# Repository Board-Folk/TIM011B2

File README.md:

# TIM-011B Version 2

A new updated remake of the TIM-011 computer from Serbia.

This repository contains the Bill-of-Materials (BOM), Gerbers and Kicad files for the new colour-capable, updated remake of the TIM-011 from the Mihajlo Pupin Institute of Serbia, 1987.

The original TIM-011 is a CP/M based computer that uses the Z80 family Hitachi HD64180 processor with 256KB RAM, 4 scale monochrome video and a FDC9266 floppy disk controller on the main board. It has an expansion bus, serial and parallel port and an ASCII keyboard interface. 

This is an adaptation of the board found at the original [TIM-011B](https://github.com/Board-Folk/TIM011B) remake repository.

In addition to the changes made to revision 1 of the project, the updated version 2 board replaces most of the video circuitry an Altera EPM7128 - CPLD logic by Marko Šolajić, including a new colour video mode. The addressing logic has also been simplified with a ATF16V8B, GAL type chip. The 8 bit IDE expansion has been added on the main board to allow the connection of a Compact Flash adapter for hard disk like use. The ROM size has been extended to allow for the use of 39SF040 also, to increase the purpose of the board with the wider range of boot ROMs and Operating Systems now available. The RAM has been changed to the now more easily available AS6C4008 and compatible SRAM.

The system can still be built entirely from off-the-shelf parts commonly available on reseller sites as no custom-made chips are used.

As of version 2.2 the overall board layout is the same as the original, but does not have the ability to drive the original CRT and doesn't provide the original Ei Niš power connector so cannot be practically used in an original case without modification.

Please see the 8bitchip [blog](https://blog.8bitchip.info/582-tim-011-v2-2-whats-new/) for more information on the version 2 update to the board. 

Projects are in Kicad 9.

## Building the board

The Kicad iBOM plugin has been used to create an interactive BOM in the BOM subfolder for the main board and expansion boards. Since these builds use obsolete parts, such as the CPU, FDC and RAM, we cannot provide any links to those parts. They are available on AliExpress and eBay, but many sellers will ship relabeled or faulty ICs. Be careful.

The Altera EPM7128 can be programmed using the JTAG header at location J2 using a USB Blaster or similar programmer with software downloadable from the Altera website. Please see Marko's Readme in the CPLD folder.

## Using the board

### Power

A 4 pin 3.96mm right angle header for 5V and 12V power where 12V is required (for an original keyboard or older model floppy drive). A centre positive DC barrel jack for 5V only operation is included also.

### Video

Three video output options are available on the version 2 board, including standard composite video output on an RCA/phono jack. 

RGBi is provided on a 9 pin female D-Sub connector and a new expansion header with RGBtoHDMI compatible pinout has been included for modules. A RP2040 based module for VGA is in the Expansion folder.

#### J7 RGBi

|Pin|Description|Notes|
|:--:|:--:|:--:|
|1|Ground||
|2|Ground||
|3|Red||
|4|Green||
|5|Blue||
|6|Intensity||
|7|Composite/CSync|JMP16|
|8|Horizontal Sync||
|9|Vertical Sync||

#### P9 RGBtoHDMI / Module

|Pin|Description|Notes|
|:--:|:--:|:--:|
|3|Ground||
|4|Intensity||
|6|Clock / N/C|JMP17|
|7|Red||
|8|Horizontal Sync||
|9|Green||
|10|Vertical Sync||
|11|Blue||
|12|+5V||

### Keyboard

The original keyboard is serial ASCII, 9600 8E1 with a 12V power output on the 5 pin DIN header. Alternative PS/2 adapters are available from the original project including a mini overlay board in the [Extensions](https://github.com/Board-Folk/TIM011B/tree/main/Extensions) folder. This has not changed from the v1.3 board layout system. There is no way of powering an original TIM-011 12V keyboard from a 5V only power source to the board.

### Sound

The sound and joystick expansion module is available in the [TIMAYSound](https://github.com/Board-Folk/TIM011B/tree/main/Extensions/TIMAYSound) folder of the original project.

### Operating System

No operating system is included within the standard TIM-011 ROM - it needs to boot this from floppy disk or equivalent Gotek/Flash Floppy or Compact Flash device. Alternative ROMs will provide different functionality.

With the larger capacity of the new ROM and jumper selection, a ROM image for multi-boot system can be made.

A TIM-011 boot ROM image can be found in the rom folder. Similarly, a sample CF card image in the cf folder and boot floppy in the floppy folder. See Marko Šolajić's [website](https://blog.8bitchip.info/tim011-resources/) for updates and more information.

## TIM011 Resources

See [TIM011 Resources](https://github.com/Board-Folk/TIM011B#tim011-resources) for links to resources from the original project.

## Revisions

* Version 2.2 Initial Public Release
  
### Version 2.1

* Dual 27512 / 39SF040 ROM size
* AS6C4008 SRAM
* Altera EPM7128 video logic
* ATF16V8B address logic
* Compact Flash Adapter header on board
* RGBtoHDMI / video expansion

### Version 2.2

* Changed all IDC to boxed headers
* Add Floppy Power Header
* Add MicroSD card header for RomWBW
* Changed Video RAM to dual footprint
* Cosmetic Adjustments

## Jumper Settings

Version 2.2

|Jumper|Description|Default|
|:--:|:--:|:--:|
|JMP1|CTS0 Select|2-3|
|JMP2|CTS/DCD Select|4-5,7-8|
|JMP4|FDC Ready|Optional|
|JMP5|Keyboard Power|1-2 D 12V, 2-3 U 5V|
|JMP9|12V Expansion Pin 40|NF|
|JMP11|Invert Sync|Off Invert, On Normal|
|JMP13|ROM A18|1-2 5V, 2-3 GND - BANK|
|JMP14|ROM A17|1-2 L 5V, 2-3 R A17|
|JMP15|ROM Write|1-2 5V, 2-3 /WR|
|JMP16|RGBI Pin 7|1 - Composite, 3 - CSYNC|
|JMP17|Clock for RGBtoHDMI Header|On/Off|

## Links

   [Marko's Blog Post on the TIM 011](https://blog.8bitchip.info/482-tim-011-a-new-life-for-an-old-computer/)

## Credits

PCB Layout by Rob Taylor @peepouk, Ian Cudlip @grandoldian and Marko Šolajić @msolajic. Schematics recreated and modifications by Ian Cudlip and Marko Šolajić. Logic by Marko Šolajić. Special thanks to @demerzel.

## Thanks

* Zoltan Pekic
* @demerzel
* The Board Folk Team

## Legal

As the product of this project is a replica of a proprietary product, the the author makes no claim of copyright to the schematics nor PCB layouts and releases these into the public domain, solely for the purposes of study and historical preservation.

You are free to produce PCBs based on this project's designs at your own risk and without limitation, for your own use or for sale and/or repair at a reasonable price. Attribution is appreciated. The authors are not obliged to provide support of any kind. 

Under no circumstances will the authors be held responsible or liable in any way for losses, damages or costs resulting from the use of the information and/or resources of this project. 

The resources are provided "as-is" without warranty of any kind, either expressed or implied, including, but not limited to, the implied warranties of merchantability and fitness for a particular purpose.

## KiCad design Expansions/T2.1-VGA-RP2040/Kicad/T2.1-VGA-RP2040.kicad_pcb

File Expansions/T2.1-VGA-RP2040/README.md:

# T2.1-VGA-RP2040

VGA Adapter for TIM-011B2 v2.1 using the RP2040 Mini. Code based on RGBI_TO_VGA by Dmitry Tsvetkov can be found on [Marko's fork for the TIM011B2](https://github.com/msolajic/RGBI_TO_VGA).

## Versions

v1 Initial version

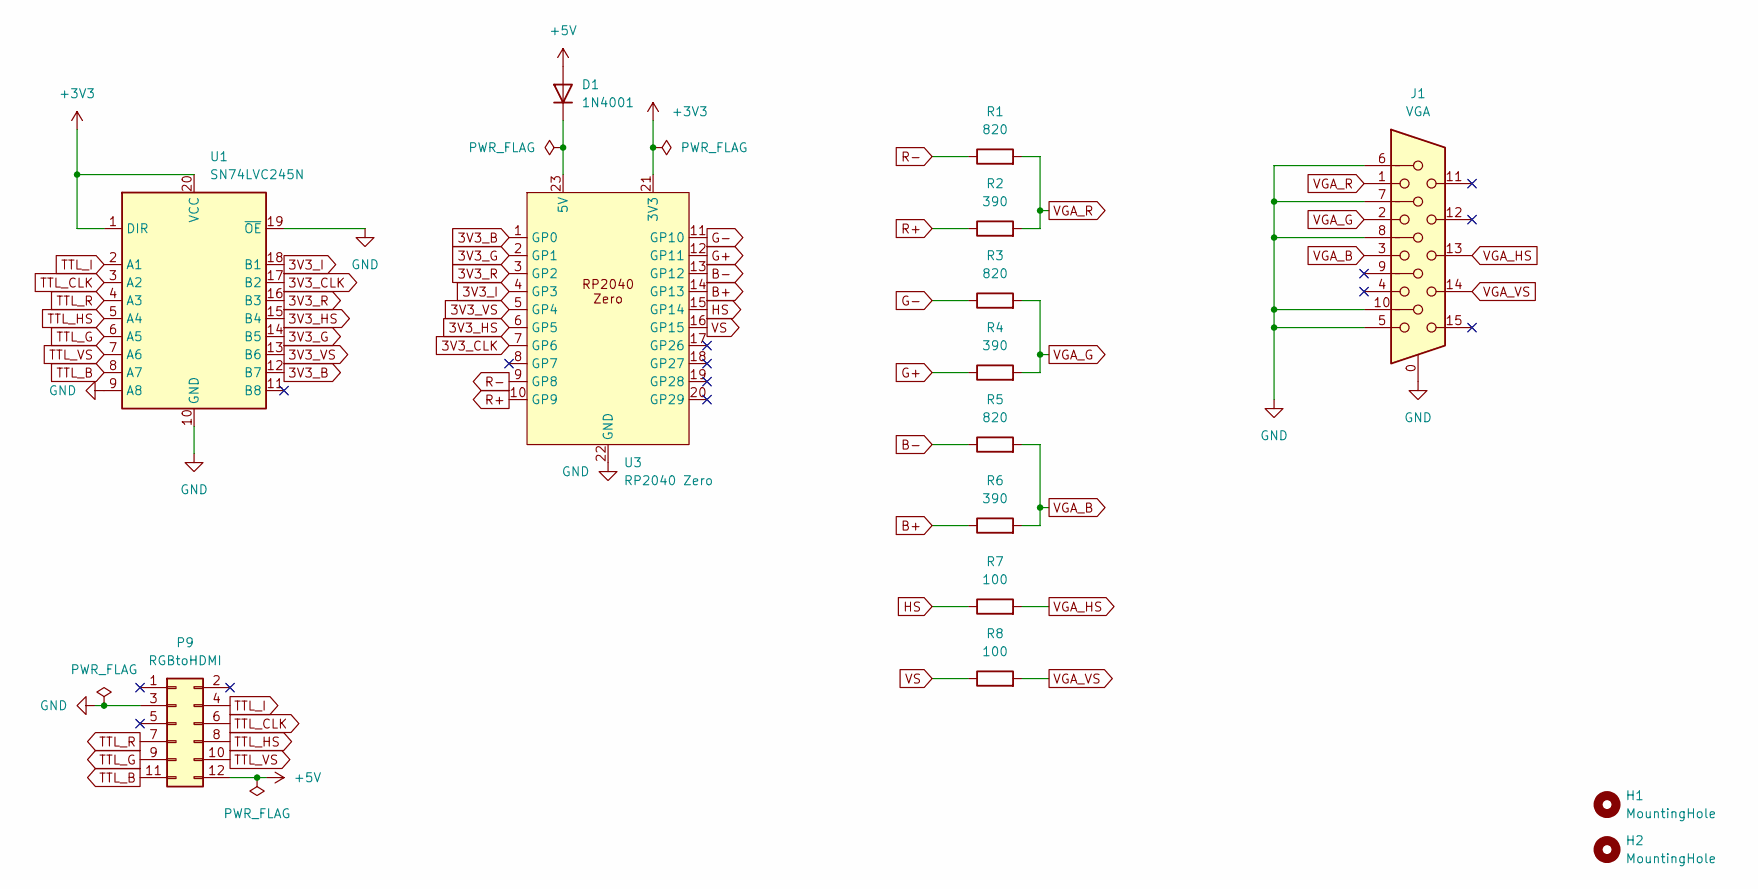
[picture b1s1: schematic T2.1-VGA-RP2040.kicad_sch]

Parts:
D1: 1N4001; TIM_D_DO-41_SOD81_P10.16mm_Horizontal
H1, H2: MountingHole; MountingHole_M2.5
J1: VGA; DSUB-15-HD_VGA_Short
P9: RGBtoHDMI; PinHeader_2x6_2.54mm
R1, R3, R5: 820; Resistor 12.7mm
R2, R4, R6: 390; Resistor 12.7mm
R7, R8: 100; Resistor 12.7mm
U1: SN74LVC245N; DIP-20_W7.62mm
U3: RP2040 Zero

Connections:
3V3_B: U1.12 (B7), U3.1 (GP0)
3V3_CLK: U1.17 (B2), U3.7 (GP6)
3V3_G: U1.14 (B5), U3.2 (GP1)
3V3_HS: U1.15 (B4), U3.6 (GP5)
3V3_I: U1.18 (B1), U3.4 (GP3)
3V3_R: U1.16 (B3), U3.3 (GP2)
3V3_VS: U1.13 (B6), U3.5 (GP4)
+3V3: U1.1 (DIR), U1.20 (VCC), U3.21 (3V3)
+5V: D1.2 (A), P9.12
B+: R6.1, U3.14 (GP13)
B-: R5.1, U3.13 (GP12)
G+: R4.1, U3.12 (GP11)
G-: R3.1, U3.11 (GP10)
GND: J1.0, J1.5, J1.6, J1.7, J1.8, J1.10, P9.3, U1.9 (A8), U1.10 (GND), U1.19 (~OE), U3.22 (GND)
HS: R7.1, U3.15 (GP14)
unnamed: D1.1 (K), U3.23 (5V)
R+: R2.1, U3.10 (GP9)
R-: R1.1, U3.9 (GP8)
TTL_B: P9.11, U1.8 (A7)
TTL_CLK: P9.6, U1.3 (A2)
TTL_G: P9.9, U1.6 (A5)
TTL_HS: P9.8, U1.5 (A4)
TTL_I: P9.4, U1.2 (A1)
TTL_R: P9.7, U1.4 (A3)
TTL_VS: P9.10, U1.7 (A6)
VGA_B: J1.3, R5.2, R6.2
VGA_G: J1.2, R3.2, R4.2
VGA_HS: J1.13, R7.2
VGA_R: J1.1, R1.2, R2.2
VGA_VS: J1.14, R8.2
VS: R8.1, U3.16 (GP15)

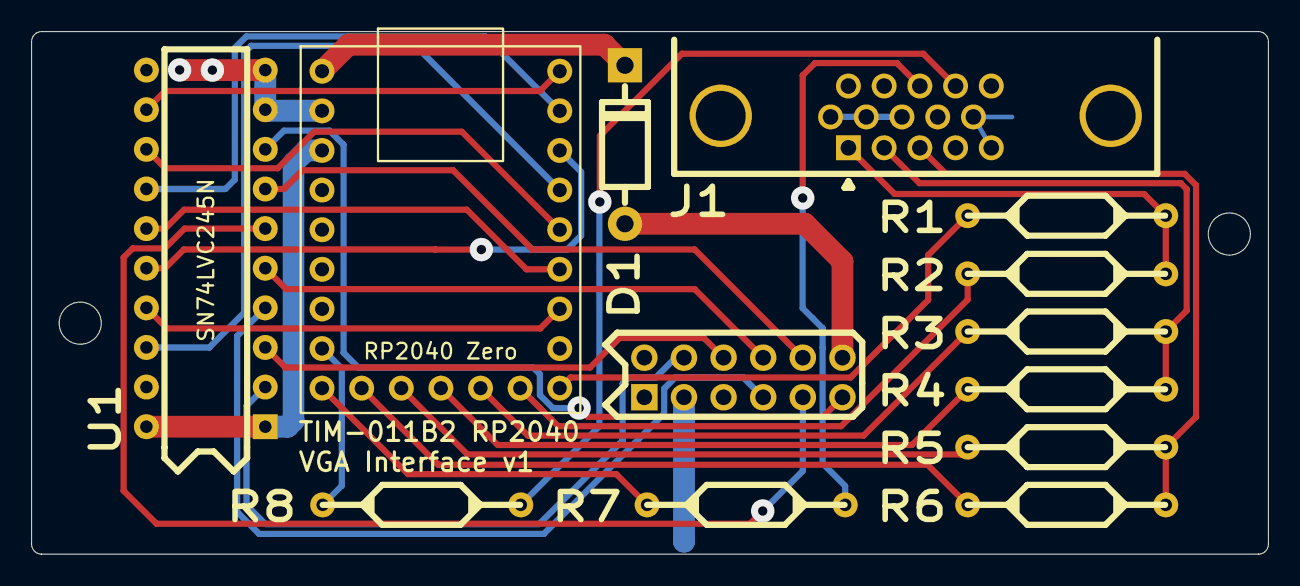
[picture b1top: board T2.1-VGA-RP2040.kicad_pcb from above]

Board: 2 copper layers, 79.3 x 33.5 mm, 15 parts (0 on the bottom side), 31 nets.

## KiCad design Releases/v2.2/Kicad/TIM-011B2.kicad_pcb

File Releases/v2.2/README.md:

# TIM-011B2 v2.2

04/11/2026

Ceramic capacitors 5.08mm and resistors 1/4W.
CPLD and GAL by Marko Šolajić (@msolajic).

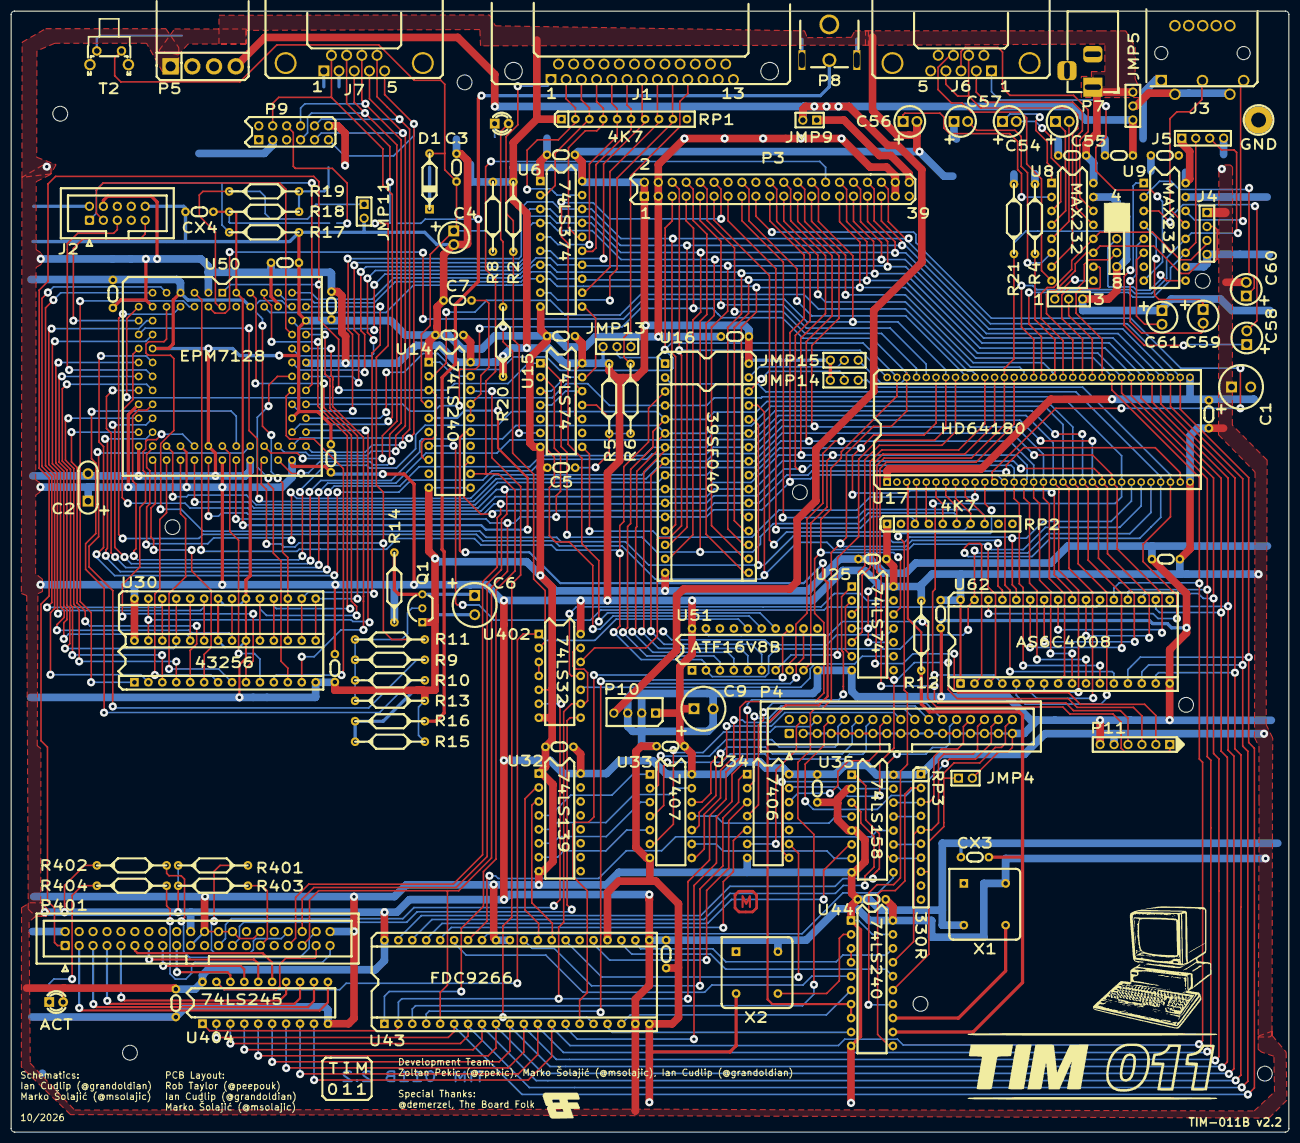
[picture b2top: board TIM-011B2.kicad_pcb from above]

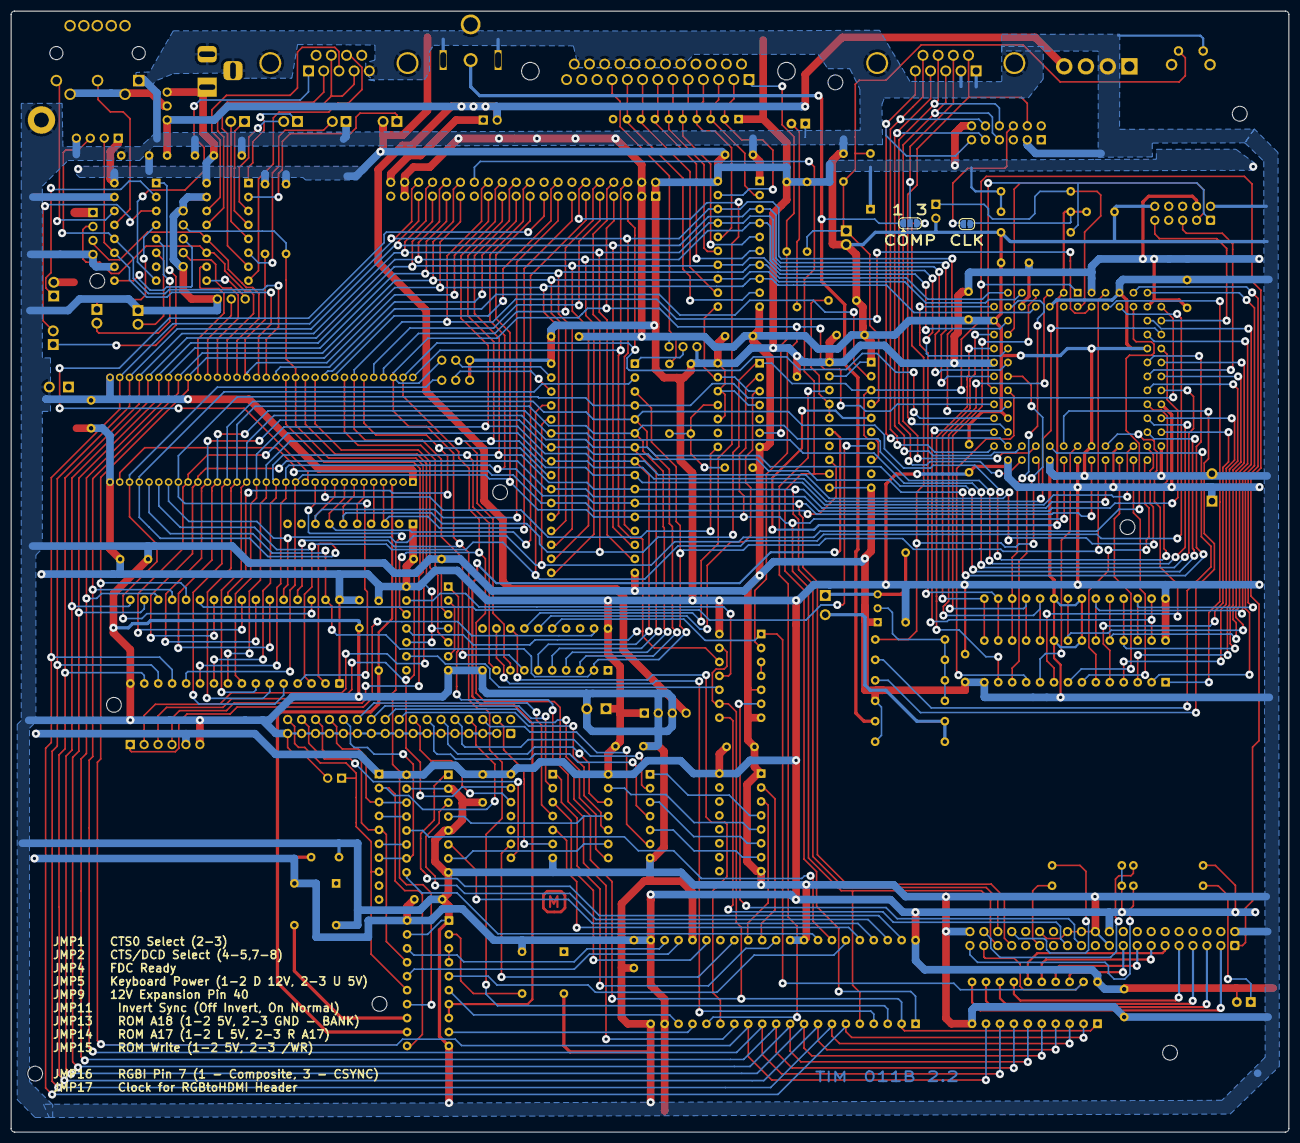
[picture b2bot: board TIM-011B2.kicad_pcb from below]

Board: 2 copper layers, 232.8 x 204.2 mm, 132 parts (2 on the bottom side), 221 nets.

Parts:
C1, C6, C9: 470uF 25V; Electrolytic Capacitor Radial 3.5mm
C2: 47uF TANT; Tantalum 5mm
C3, C7, C8, C14, C15, C16, C19, C20, C23, C24, C25, C30, C31, C36, C41, C42, C43, C44, C48, C49, C50, C51, C53, C62: 100nF; Ceramic Cap 5.08mm
C4: 10uF; Electrolytic Capacitor Radial
C5: 2n2; Ceramic Cap 5.08mm
C54, C55, C56, C57, C58, C59, C60, C61: 1uF; Electrolytic Capacitor Radial
CX3, CX4: 330pF; Ceramic Cap 5.08mm
D1: 1N4148; Diode 10.16mm
D2: POWER; TIM_LED_D3.0mm
D401: ACT; TIM_LED_D3.0mm
G1: Board Folk Logo; BF8
G2: TIM011 Logo; tim011logo
G3: TIM011 Picture; tim011_picture
H1, H2, H4, H5, H6, H7, H8, H9, H10: MountingHole; MountingHole_M2.5
H3: GND; TIM_MountingHole_2.7mm_Pad
J1: PRINTER
J2: JTAG; JTAG Header 2x05
J3: TASTATURA; KEYBOARD2
J4: SERIAL; PinHeader_1x04_2.54mm
J5: KBD; PinHeader_1x04_2.54mm
J6: RS-232/9; SERIAL9
J7: RGBI OUT; VIDEO9
JMP1: CTS0 Select; PinHeader_1x03 2.54mm
JMP2: CTS/DCD Select; PinHeader_1x05_2.54mm_Alt
JMP4: FDC Ready; PinHeader_1x02 2.54mm
JMP5: KBPWR; PinHeader_1x03 2.54mm
JMP9: 12VEXP; PinHeader_1x02 2.54mm
JMP11: INVERT SYNC; PinHeader_1x02 2.54mm
JMP13: ROMA18; PinHeader_1x03 2.54mm
JMP14: ROMA17; PinHeader_1x03 2.54mm
JMP15: ROM WR; PinHeader_1x03 2.54mm
JMP16: COMP; SolderJumper-3_P1.3mm_Open_RoundedPad1.0x1.5mm
JMP17: CLK; SolderJumper-2_P1.3mm_Open_RoundedPad1.0x1.5mm
P3: EXPAND; PinHeader_2x20 2.54mm
P4: DISK; FDD Header 2x17
P5: POWER; 3.96mm Header 4-Pin Edge
P7: 5V Jack; TIM_BarrelJack_Horizontal
P8: Composite; RCA2
P9: RGBtoHDMI; PinHeader_2x6_2.54mm
P10: FLOPPY POWER; PinHeader_1x04_2.54mm_Power Box
P11: MicroSD; PinHeader_1x06 2.54mm
P401: IDE/CF; IDE Header 2x20
Q1: BC557; TO-92_Inline_Wide
R2, R4, R5, R401, R402, R403: 4K7; Resistor 12.7mm
R6: 100R; Resistor 12.7mm
R8: 1M; Resistor 12.7mm
R9: 2K2; Resistor 12.7mm
R10: 1K5; Resistor 12.7mm
R11: 5K1; Resistor 12.7mm
R12, R18: 470R; Resistor 12.7mm
R13, R20, R404: 1K; Resistor 12.7mm
R14: 220R; Resistor 12.7mm
R15, R17, R19, R21: 10K; Resistor 12.7mm
R16: 68R; Resistor 12.7mm
RP1, RP2: 4K7; R_Array_SIP10
RP3: 330R; R_Array_SIP10
T2: RESET; New Reset
U6: 74LS374; DIP-20_W7.62mm
U8, U9: MAX232; DIP-16_W7.62mm
U14, U44: 74LS240; DIP-20_W7.62mm
U15, U25: 74LS74; DIP-14_W7.62mm
U16: 39SF040; DIP-32_W15.24mm_Dual
U17: HD64180; DIP-64_1.78mm Pitch_Socket
U30: 43256; DIP-28_Dual_Socket
U32: 74LS139; DIP-16_W7.62mm
U33: 74LS07; DIP-14_W7.62mm
U34: 74LS06; DIP-14_W7.62mm
U35: 74LS158; DIP-16_W7.62mm
U43: FDC9266; DIP-40_W15.24mm_Socket
U50: EPM7128; PLCC-84_THT-Socket
U51: ATF16V8B; DIP-20_W7.62mm
U62: AS6C4008-55PCN; DIP-32_W15.24mm
U402: 74LS32; DIP-14_W7.62mm
U404: 74LS245; DIP-20_W7.62mm
X1: 12.288MHz; TIM_Oscillator_DIP-8
X2: 8MHz; TIM_Oscillator_DIP-8

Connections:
+5V: C1.1, C2.1, C9.1, C14.1, C15.1, C16.1, C19.1, C20.1, C23.1, C24.1, C25.1, C30.1, C31.1, C36.1, C41.1, C42.1, C43.1, C44.1, C48.1, C49.1, C50.1, C51.1, C53.1, C56.2, C60.2, C62.1, D1.1 (K), D401.2 (A), J2.4, J4.1, J5.1, JMP5.3, JMP13.1, JMP14.1, JMP15.1, P3.1, P3.2, P5.1, P7.1, P9.12, P10.1, P11.5, P401.20, R2.1, R4.1, R5.1, R8.1, R12.1, R14.1, R18.1, R19.2, R20.1, R21.1, R401.1, R402.1, R403.1, RP1.1 (common), RP2.1 (common), RP3.1 (common), U6.20 (VCC), U8.16 (VCC), U9.16 (VCC), U14.20 (VCC), U15.4 (~S), U15.10 (~S), U15.12 (D), U15.14 (VCC), U16.32 (VCC), U17.32 (Vcc), U25.4 (~S), U25.10 (~S), U25.14 (VCC), U30.28 (VCC), U32.16 (VCC), U33.14 (VCC), U34.14 (VCC), U35.16 (VCC), U43.19 (TEST), U43.21 (MINI), U43.40 (VCC), U44.20 (VCC), U50.3 (VCC), U50.13 (VCC), U50.26 (VCC), U50.38 (VCC), U50.43 (VCC), U50.53 (VCC), U50.66 (VCC), U50.78 (VCC), U51.20 (V_{CC}), U62.1 (A18), U62.32 (VCC), U402.14 (VCC), U404.20 (VCC), X1.8 (Vcc), X2.8 (Vcc)
+12V: C8.1, JMP5.1, JMP9.2, P5.4, P10.4
/Addressing/A0: P3.19, P401.35, U15.2 (D), U16.12 (A0), U17.13 (A0), U43.5 (A0), U50.45 (IO), U62.12 (A0)
/Addressing/A1: P3.20, P401.33, U16.11 (A1), U17.14 (A1), U50.41 (IO), U62.11 (A1)
/Addressing/A2: P3.22, P401.36, U16.10 (A2), U17.15 (A2), U50.39 (IO), U51.9 (I8), U62.10 (A2)
/Addressing/A3: P3.23, U16.9 (A3), U17.16 (A3), U50.36 (IO), U51.8 (I7), U62.9 (A3)
/Addressing/A4: P3.24, U16.8 (A4), U17.17 (A4), U50.34 (IO), U51.6 (I5), U62.8 (A4)
/Addressing/A5: U16.7 (A5), U17.18 (A5), U50.31 (IO), U51.5 (I4), U62.7 (A5)
/Addressing/A6: U16.6 (A6), U17.19 (A6), U50.29 (IO), U51.4 (I3), U62.6 (A6)
/Addressing/A7: U16.5 (A7), U17.20 (A7), U50.27 (IO), U51.3 (I2), U62.5 (A7)
/Addressing/A8: U16.27 (A8), U17.21 (A8), U50.24 (IO), U62.27 (A8)
/Addressing/A9: U16.26 (A9), U17.22 (A9), U50.21 (IO), U62.26 (A9)
/Addressing/A10: U16.23 (A10), U17.23 (A10), U50.18 (IO), U62.23 (A10)
/Addressing/A11: U16.25 (A11), U17.24 (A11), U50.16 (IO), U62.25 (A11)
/Addressing/A12: U16.4 (A12), U17.25 (A12), U50.12 (IO), U62.4 (A12)
/Addressing/A13: U16.28 (A13), U17.26 (A13), U50.10 (IO), U62.28 (A13)
/Addressing/A14: U16.29 (A14), U17.27 (A14), U50.8 (IO), U62.3 (A14)
/Addressing/A15: U16.3 (A15), U17.28 (A15), U50.5 (IO), U51.2 (I1), U62.31 (A15)
/Addressing/A16: U16.2 (A16), U17.29 (A16), U62.2 (A16)
/Addressing/A17: JMP14.3, U17.30 (A17), U62.30 (A17)
/Addressing/A18: U14.13, U16.22 (CE), U17.31 (A18/TOUT)
/CPU/CLK: CX3.1, R12.2, U17.3 (EXTAL), U44.12
/CPU/D0: P3.36, U6.18 (D7), U16.13 (D0), U17.34 (D0), U43.6 (DB0), U50.61 (IO), U62.13 (DQ0), U404.2 (A0)
/CPU/D1: P3.35, U6.3 (D0), U16.14 (D1), U17.35 (D1), U43.7 (DB1), U50.64 (IO), U62.14 (DQ1), U404.3 (A1)
/CPU/D2: P3.34, U6.17 (D6), U16.15 (D2), U17.36 (D2), U43.8 (DB2), U50.67 (IO), U62.15 (DQ2), U404.4 (A2)
/CPU/D3: P3.32, U6.4 (D1), U16.17 (D3), U17.37 (D3), U43.9 (DB3), U50.69 (IO), U62.17 (DQ3), U404.5 (A3)
/CPU/D4: P3.33, U6.14 (D5), U16.18 (D4), U17.38 (D4), U43.10 (DB4), U50.73 (IO), U62.18 (DQ4), U404.6 (A4)
/CPU/D5: P3.31, U6.7 (D2), U16.19 (D5), U17.39 (D5), U43.11 (DB5), U50.75 (IO), U62.19 (DQ5), U404.7 (A5)
/CPU/D6: P3.30, U6.13 (D4), U16.20 (D6), U17.40 (D6), U43.12 (DB6), U50.77 (IO), U62.20 (DQ6), U404.8 (A6)
/CPU/D7: P3.29, U6.8 (D3), U16.21 (D7), U17.41 (D7), U43.13 (DB7), U50.80 (IO), U62.21 (DQ7), U404.9 (A7)
/CPU/~CLK: U14.15, U44.7, U44.8
/EPM7128/IO0: U30.11 (Q0), U50.63 (IO)
/EPM7128/IO1: U30.12 (Q1), U50.65 (IO)
/EPM7128/IO2: U30.13 (Q2), U50.68 (IO)
/EPM7128/IO3: U30.15 (Q3), U50.70 (IO)
/EPM7128/IO4: U30.16 (Q4), U50.74 (IO)
/EPM7128/IO5: U30.17 (Q5), U50.76 (IO)
/EPM7128/IO6: U30.18 (Q6), U50.79 (IO)
/EPM7128/IO7: U30.19 (Q7), U50.81 (IO)
/EPM7128/VA0: U30.10 (A0), U50.44 (IO)
/EPM7128/VA1: U30.9 (A1), U50.40 (IO)
/EPM7128/VA2: U30.8 (A2), U50.37 (IO)
/EPM7128/VA3: U30.7 (A3), U50.35 (IO)
/EPM7128/VA4: U30.6 (A4), U50.33 (IO)
/EPM7128/VA5: U30.5 (A5), U50.30 (IO)
/EPM7128/VA6: U30.4 (A6), U50.28 (IO)
/EPM7128/VA7: U30.3 (A7), U50.25 (IO)
/EPM7128/VA8: U30.25 (A8), U50.22 (IO)
/EPM7128/VA9: U30.24 (A9), U50.20 (IO)
/EPM7128/VA10: U30.21 (A10), U50.17 (IO)
/EPM7128/VA11: U30.23 (A11), U50.15 (IO)
/EPM7128/VA12: U30.2 (A12), U50.11 (IO)
/EPM7128/VA13: U30.26 (A13), U50.9 (IO)
/EPM7128/VA14: U30.1 (A14), U50.6 (IO)
/Expansion/BD0: P401.17, U404.18 (B0)
/Expansion/BD1: P401.15, U404.17 (B1)
/Expansion/BD2: P401.13, U404.16 (B2)
/Expansion/BD3: P401.11, U404.15 (B3)
/Expansion/BD4: P401.9, U404.14 (B4)
/Expansion/BD5: P401.7, U404.13 (B5)
/Expansion/BD6: P401.5, U404.12 (B6)
/Expansion/BD7: P401.3, U404.11 (B7)
/Video/OFFSETC: C6.1, Q1.3 (E), R14.2
CKS: P11.2, U17.53 (CKS)
CLK8: U43.22 (CLK), U44.18
CPLDCLK: CX4.1, JMP17.2 (B), R18.2, U14.5, U50.83 (GCLK)
E: P3.9, U17.60 (E)
EXPSEL_O: P3.12, U51.14 (I/O)
FDCDMA_0: U43.15 (~DACK), U51.13 (I/O)
FDCSEL_0: U43.4 (~CS), U51.12 (I/O)
FI: P3.6, U17.64 (Ø), U25.11 (C), U402.12
GND: C1.2, C2.2, C3.2, C4.2, C5.2, C7.2, C8.2, C9.2, C14.2, C15.2, C16.2, C19.2, C20.2, C23.2, C24.2, C25.2, C30.2, C31.2, C36.2, C41.2, C42.2, C43.2, C44.2, C48.2, C49.2, C50.2, C51.2, C53.2, C57.1, C61.1, C62.2, CX3.2, CX4.2, D2.1 (K), H3.1, J1.18, J1.19, J1.20, J1.21, J1.22, J1.23, J1.24, J1.25, J2.2, J2.10, J3.1, J4.4, J5.4, J6.0 (PAD), J6.5, J7.0 (PAD), J7.1, J7.2, JMP1.3, JMP2.1, JMP2.5, JMP4.2, JMP11.2, JMP13.3, P3.3, P3.4, P3.37, P3.38, P4.3, P4.5, P4.7, P4.9, P4.11, P4.13, P4.15, P4.17, P4.19, P4.21, P4.23, P4.25, P4.27, P4.29, P4.31, P4.33, P5.2, P7.2, P7.3, P8.2 (Ext), P9.3, P10.2, P10.3, P11.6, P401.2, P401.19, P401.22, P401.24, P401.26, P401.30, P401.40, Q1.1 (C), R13.2, R15.2, R17.2, T2.1, U6.1 (OE), U6.10 (GND), U8.15 (GND), U9.10 (T2IN), U9.15 (GND), U14.1, U14.10 (GND), U14.11, U14.19, U15.7 (GND), U16.16 (GND), U17.1 (Vss), U17.33 (Vss), U25.7 (GND), U30.14 (GND), U30.20 (~CS), U30.22 (~OE), U32.1 (E), U32.8 (GND), U33.7 (GND), U34.7 (GND), U35.2 (I0a), U35.5 (I0b), U35.8 (GND), U35.15 (E), U43.20 (VSS), U43.24 (P0), U43.31 (P1), U43.32 (P2), U44.1, U44.10 (GND), U44.19, U50.7 (GND), U50.19 (GND), U50.32 (GND), U50.42 (GND), U50.47 (GND), U50.59 (GND), U50.72 (GND), U50.82 (GND), U51.10 (GND), U62.16 (VSS), U402.5, U402.7 (GND), U404.10 (GND), X1.4 (GND), X2.4 (GND)
INVERT: JMP11.1, R19.1, U50.2 (OE2n)
J_CTS: J6.8, U8.8 (R2IN)
J_DCD: J6.1, U9.8 (R2IN)
J_RTS: J6.4, J6.7, U8.7 (T2OUT)
J_RX: J6.2, U8.13 (R1IN)
J_TX: J6.3, U8.14 (T1OUT)
K_RX: J3.2, U9.13 (R1IN)
K_TX: J3.3, U9.14 (T1OUT)
unnamed: C6.2, R15.1, R16.1
unnamed: C7.1, U14.16, U14.17
unnamed: C3.1, C4.1, D1.2 (A), R8.2, T2.2, U14.4
unnamed: D2.2 (A), R20.2
unnamed: D401.1 (K), R404.1
unnamed: J1.10, R6.2
unnamed: J3.4, J3.5, JMP5.2
unnamed: JMP9.1, P3.40
unnamed: JMP13.2, U16.1 (A18)
unnamed: JMP14.2, U16.30 (A17)
unnamed: JMP15.2, U16.31 (PGM)
unnamed: J7.7, JMP16.2
unnamed: JMP17.1 (A), P9.6
unnamed: P401.23, U402.6
unnamed: P401.25, U402.8
unnamed: P401.29, R403.2
unnamed: P401.34, R401.2
unnamed: P401.38, R402.2
unnamed: P401.39, R404.2
unnamed: Q1.2 (B), R9.1, R10.1, R11.1, R13.1
unnamed: J1.2, RP1.2 (R1), U6.19 (O7)
unnamed: J1.3, RP1.3 (R2), U6.2 (O0)
unnamed: J1.4, RP1.4 (R3), U6.16 (O6)
unnamed: J1.5, RP1.5 (R4), U6.5 (O1)
unnamed: J1.6, RP1.6 (R5), U6.15 (O5)
unnamed: J1.7, RP1.7 (R6), U6.6 (O2)
unnamed: J1.8, RP1.8 (R7), U6.12 (O4)
unnamed: J1.9, RP1.9 (R8), U6.9 (O3)
unnamed: RP3.4 (R3), U35.13 (I1c)
unnamed: RP3.6 (R5), U35.11 (I0d)
unnamed: C54.1, U8.1 (C1+)
unnamed: C54.2, U8.3 (C1-)
unnamed: C55.1, U8.4 (C2+)
unnamed: C55.2, U8.5 (C2-)
unnamed: C56.1, U8.2 (VS+)
unnamed: C57.2, U8.6 (VS-)
unnamed: C58.1, U9.1 (C1+)
unnamed: C58.2, U9.3 (C1-)
unnamed: C59.1, U9.4 (C2+)
unnamed: C59.2, U9.5 (C2-)
unnamed: C60.1, U9.2 (VS+)
unnamed: C61.2, U9.6 (VS-)
unnamed: J1.1, R2.2, U15.6 (~Q)
unnamed: C5.1, R5.2, R6.1, U15.11 (C)
unnamed: U25.2 (D), U25.6 (~Q)
unnamed: U25.1 (~R), U43.14 (DRQ)
unnamed: U25.9 (Q), U402.10
unnamed: U25.13 (~R), U402.11
unnamed: U32.2 (A0), U43.29 (DS0)
unnamed: U32.3 (A1), U43.28 (DS1)
unnamed: U32.4 (O0), U33.1
unnamed: U32.5 (O1), U33.13
unnamed: U32.6 (O2), U33.3
unnamed: U32.7 (O3), U33.5
unnamed: U35.3 (I1a), U43.38 (LCT_DIR)
unnamed: U35.6 (I1b), U43.37 (STEP)
unnamed: U35.1 (S), U43.39 (~RW_SEEK)
unnamed: U33.11, U35.4 (Za)
unnamed: U33.9, U35.7 (Zb)
unnamed: U35.12 (Zc), U43.34 (WP/TS)
unnamed: U35.9 (Zd), U43.33 (FLT/TR0)
unnamed: U34.5, U43.36 (HDL)
unnamed: U43.17 (IDX), U44.9
unnamed: U43.18 (INT), U44.6
unnamed: U43.35 (RDY), U44.5
unnamed: U34.9, U43.27 (SIDE)
unnamed: U14.18, U43.16 (TC)
unnamed: U34.1, U43.30 (WDOUT)
unnamed: U34.3, U43.25 (WE)
unnamed: U43.23 (~DSKD), U44.16
unnamed: U44.3, U44.4
unnamed: U14.7, U62.22 (CE#)
unnamed: U402.3, U402.4
unnamed: U44.13, X1.5 (OUT)
unnamed: U44.2, X2.5 (OUT)
OUT_B: J7.5, P9.11, U50.55 (IO)
OUT_G: J7.4, P9.9, U50.52 (IO)
OUT_I: J7.6, P9.4, U50.57 (IO)
OUT_R: J7.3, P9.7, U50.50 (IO)
PRINT_O: U6.11 (Cp), U15.3 (C), U15.13 (~R), U51.15 (I/O)
RESET: P3.28, U14.12, U43.1 (RST)
RX0: J4.3, U8.12 (R1OUT), U17.46 (RXA0)
RX1: J5.3, U9.12 (R1OUT), U17.49 (RXA1)
RXS/~CTS1: JMP2.2, P11.4, R21.2, U17.52 (RXS/~CTS1)
ST: P3.17, U17.12 (ST)
TCK: J2.1, R17.1, U50.62 (IO)
TDI: J2.9, U50.14 (IO)
TDO: J2.3, U50.71 (IO)
TMS: J2.5, U50.23 (IO)
TX0: J4.2, U8.11 (T1IN), U17.45 (TXA0)
TX1: J5.2, U9.11 (T1IN), U17.48 (TXA1)
TXS: P11.3, U17.51 (TXS), U34.13
VID1: R10.2, U50.46 (IO)
VID2: R9.2, U50.48 (IO)
X_CTS: JMP1.1, U8.9 (R2OUT)
X_DCD: JMP2.3, U9.9 (R2OUT)
fDIR: P4.18, U33.10
fDRIVE0: P4.10, U33.2
fDRIVE1: P4.12, U33.12
fDRIVE2: P4.14, U33.4
fDRIVE3: P4.6, U33.6
fINDEX: P4.8, RP3.2 (R1), U44.11
fINUSE: P4.4, U34.6
fMOTOR1: P4.16, U34.12
fREAD: P4.30, RP3.5 (R4), U44.17
fREADY: JMP4.1, P4.34, RP3.8 (R7), U44.15
fSIDE1: P4.32, U34.8
fSTEP: P4.20, U33.8
fTRACK0: P4.26, RP3.7 (R6), U35.10 (I1d)
fWDATA: P4.22, U34.2
fWGATE: P4.24, U34.4
fWRITEPROT: P4.28, RP3.3 (R2), U35.14 (I0c)
~BUSACK: RP2.4 (R3), U17.5 (~BUSACK)
~BUSREQ: RP2.5 (R4), U17.6 (~BUSREQ)
~COMP: JMP16.1, P8.1 (In), R16.2
~CSYNC: JMP16.3, R11.2, U50.49 (IO)
~CTS0: JMP1.2, U17.43 (~CTS0)
~DCD0: JMP2.4, U17.44 (~DCD0)
~DREQ0: P3.25, R4.2, U17.47 (CKA0/~DREQ0)
~DREQ1: U17.54 (~DREQ1), U25.5 (Q)
~HALT: P3.16, U17.56 (~HALT)
~HSYNC: J7.8, P9.8, U50.51 (IO)
~IDE_CS: P401.37, U51.16 (I/O), U402.1, U404.19 (CE)
~INT0: P3.15, RP2.8 (R7), U17.9 (~INT0)
~INT1: U15.8 (~Q), U17.10 (~INT1)
~INT2: U17.11 (~INT2), U44.14
~IOE: P3.26, U17.58 (~IOE), U50.4 (IO), U51.7 (I6)
~LIR: P3.10, U17.61 (~LIR)
~ME: U16.24 (OE), U17.59 (~ME), U62.24 (OE#)
~NMI: P3.11, RP2.7 (R6), U17.8 (~NMI)
~RD: P3.5, U17.63 (~RD), U25.12 (D), U43.2 (~RD), U50.58 (IO), U402.9, U402.13, U404.1 (A->B)
~REF: U17.57 (~REF), U25.3 (C)
~RESET: P3.8, P401.1, RP2.6 (R5), U14.3, U14.8, U15.1 (~R), U17.7 (~RESET), U50.1 (GCLRn)
~RTS0: U8.10 (T2IN), U17.42 (~RTS0)
~SD_CS: P11.1, U51.19 (I/O)
~TEND0: P3.21, U17.50 (CKA1/~TEND0)
~TEND1: U14.2, U17.55 (~TEND1)
~VSYNC: J7.9, P9.10, U50.54 (IO)
~VWR: U30.27 (~WE), U50.56 (IO)
~WAIT: P3.13, RP2.3 (R2), U17.4 (~WAIT)
~WR: JMP15.3, P3.7, U17.62 (~WR), U43.3 (~WR), U50.60 (IO), U62.29 (WE#), U402.2

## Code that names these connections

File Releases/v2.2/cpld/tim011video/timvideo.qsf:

# -------------------------------------------------------------------------- #
#
# Copyright (C) 1991-2013 Altera Corporation
# Your use of Altera Corporation's design tools, logic functions 
# and other software and tools, and its AMPP partner logic 
# functions, and any output files from any of the foregoing 
# (including device programming or simulation files), and any 
# associated documentation or information are expressly subject 
# to the terms and conditions of the Altera Program License 
# Subscription Agreement, Altera MegaCore Function License 
# Agreement, or other applicable license agreement, including, 
# without limitation, that your use is for the sole purpose of 
# programming logic devices manufactured by Altera and sold by 
# Altera or its authorized distributors.  Please refer to the 
# applicable agreement for further details.
#
# -------------------------------------------------------------------------- #
#
# Quartus II 64-Bit
# Version 13.0.1 Build 232 06/12/2013 Service Pack 1 SJ Web Edition
# Date created = 11:33:50  February 03, 2026
#
# -------------------------------------------------------------------------- #
#
# Notes:
#
# 1) The default values for assignments are stored in the file:
#		timvideo_assignment_defaults.qdf
#    If this file doesn't exist, see file:
#		assignment_defaults.qdf
#
# 2) Altera recommends that you do not modify this file. This
#    file is updated automatically by the Quartus II software
#    and any changes you make may be lost or overwritten.
#
# -------------------------------------------------------------------------- #


set_global_assignment -name FAMILY MAX7000S
set_global_assignment -name DEVICE "EPM7128SLC84-15"
set_global_assignment -name TOP_LEVEL_ENTITY timvideo
set_global_assignment -name ORIGINAL_QUARTUS_VERSION "13.0 SP1"
set_global_assignment -name PROJECT_CREATION_TIME_DATE "11:33:50  FEBRUARY 03, 2026"
set_global_assignment -name LAST_QUARTUS_VERSION "13.0 SP1"
set_global_assignment -name PROJECT_OUTPUT_DIRECTORY output_files
set_global_assignment -name ERROR_CHECK_FREQUENCY_DIVISOR "-1"
set_global_assignment -name MAX7000_DEVICE_IO_STANDARD TTL
set_global_assignment -name BDF_FILE timvideo.bdf
set_global_assignment -name QIP_FILE hcount.qip
set_global_assignment -name QIP_FILE vcount.qip
set_global_assignment -name QIP_FILE addrmux.qip
set_global_assignment -name QIP_FILE scradd.qip
set_location_assignment PIN_83 -to CLK
set_location_assignment PIN_6 -to VA[14]
set_location_assignment PIN_9 -to VA[13]
set_location_assignment PIN_11 -to VA[12]
set_location_assignment PIN_15 -to VA[11]
set_location_assignment PIN_17 -to VA[10]
set_location_assignment PIN_20 -to VA[9]
set_location_assignment PIN_22 -to VA[8]
set_location_assignment PIN_25 -to VA[7]
set_location_assignment PIN_28 -to VA[6]
set_location_assignment PIN_30 -to VA[5]
set_location_assignment PIN_33 -to VA[4]
set_location_assignment PIN_35 -to VA[3]
set_location_assignment PIN_37 -to VA[2]
set_location_assignment PIN_40 -to VA[1]
set_location_assignment PIN_44 -to VA[0]
set_location_assignment PIN_45 -to A[0]
set_location_assignment PIN_41 -to A[1]
set_location_assignment PIN_39 -to A[2]
set_location_assignment PIN_36 -to A[3]
set_location_assignment PIN_34 -to A[4]
set_location_assignment PIN_31 -to A[5]
set_location_assignment PIN_29 -to A[6]
set_location_assignment PIN_27 -to A[7]
set_location_assignment PIN_24 -to A[8]
set_location_assignment PIN_21 -to A[9]
set_location_assignment PIN_18 -to A[10]
set_location_assignment PIN_16 -to A[11]
set_location_assignment PIN_12 -to A[12]
set_location_assignment PIN_10 -to A[13]
set_location_assignment PIN_8 -to A[14]
set_location_assignment PIN_5 -to A[15]
set_location_assignment PIN_80 -to D[7]
set_location_assignment PIN_77 -to D[6]
set_location_assignment PIN_75 -to D[5]
set_location_assignment PIN_73 -to D[4]
set_location_assignment PIN_69 -to D[3]
set_location_assignment PIN_67 -to D[2]
set_location_assignment PIN_64 -to D[1]
set_location_assignment PIN_61 -to D[0]
set_location_assignment PIN_81 -to VD[7]
set_location_assignment PIN_79 -to VD[6]
set_location_assignment PIN_76 -to VD[5]
set_location_assignment PIN_74 -to VD[4]
set_location_assignment PIN_70 -to VD[3]
set_location_assignment PIN_68 -to VD[2]
set_location_assignment PIN_65 -to VD[1]
set_location_assignment PIN_63 -to VD[0]
set_location_assignment PIN_58 -to nRD
set_location_assignment PIN_60 -to nWR
set_location_assignment PIN_56 -to vWR
set_location_assignment PIN_46 -to VID1
set_location_assignment PIN_48 -to VID2
set_location_assignment PIN_49 -to CSYNC
set_location_assignment PIN_1 -to nRESET
set_global_assignment -name OPTIMIZE_HOLD_TIMING OFF
set_global_assignment -name OPTIMIZE_MULTI_CORNER_TIMING OFF
set_global_assignment -name FITTER_EFFORT "STANDARD FIT"
set_global_assignment -name SLOW_SLEW_RATE OFF
set_location_assignment PIN_4 -to nIOE
set_location_assignment PIN_51 -to HSYNC
set_location_assignment PIN_54 -to VSYNC
set_location_assignment PIN_50 -to OUT_R
set_location_assignment PIN_52 -to OUT_G
set_global_assignment -name QIP_FILE output_files/lpm_add_sub0.qip
set_location_assignment PIN_55 -to OUT_B
set_location_assignment PIN_57 -to OUT_I
set_location_assignment PIN_2 -to SYNC_SEL
